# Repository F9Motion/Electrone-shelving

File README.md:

# RGB Lamp

A electronic shelving (1.8m) to put your other projects here. This is simple shelving called electronic because the shleving have a 8 RGB Lamps in top every shelf. You can just download materials and print/solder this :)

## Why I made this
I find shelving like this in marketplace but not electronic and take idea :D

## Features

- 7 modes: Aqua, White, Yellow, Red, Purple, Blue, Green, Lime, Indigo, Soft Peach
- Brightness from 10% to 100% in steps of 10%
- Settings (mode and brightness) are saved and restored after power loss
- Custom round PCB designed in KiCad
- USB-C powered

## Pictures

### Full 3D model

### PCB

## How it works
It works (RGB Lamps) with batery and firmware. Without firmware this shelving transforms to defoult shelving. Prease use with firmware!

## Controls

| Action                          | Result                          |
|---------------------------------|---------------------------------|
| Button 1: hold for 2 seconds    | Turn the lamp on / off (fade)   |
| Button 1: short press           | Next mode                       |
| Button 1: double press          | Brightness +10%                 |
| Button 2: short press           | Previous mode                   |
| Button 2: quick repeated press  | Brightness −10%                 |

## How to assemble
1. Print the PCB from JLPPCB's website or app
2. Print all .step files
3. Upload firmware to PCB
4. Collect all components(Take a look at the screenshots if you're having trouble)
5. Place it on your room and continue doing your other projects.

## Role of hack club
All this project will be sponsered by Hack club forge. A lot of thanks for you. You helped me do my dreams in real life. Hack club is working since 2015 so A new era of engineers is approaching. 

## How to flash

1. Install [Thonny](https://thonny.org/).
2. Flash MicroPython to the ESP32 (Thonny: *Tools → Options → Interpreter → Install or update MicroPython*).
3. Open `firmware/firmware.py` in Thonny.
4. Save it to the board as `main.py` (*File → Save as → MicroPython device*).
5. Restart the board. The OLED shows a loading bar and the lamp is ready.

## Bill of Materials (BOM)
|Name                                |Cost   |Link                                                                                                                                                           |
|------------------------------------|-------|---------------------------------------------------------------------------------------------------------------------------------------------------------------|
|ESP32 C3                            |$1.8   |https://aliexpress.ru/item/1005007676793679.html?shpMethod=AE_CN_SUPER_ECONOMY_G&sku_id=12000041769821205&spm=a2g2w.productlist.search_results.4.677f53633EnYjH|
|Diodes 1n4148                       |$0.7   |https://aliexpress.ru/item/1005007807649334.html?shpMethod=AE_CN_SUPER_ECONOMY_G&sku_id=12000042270438468&spm=a2g2w.productlist.search_results.2.1b7fad9fg6OJxq|
|RGB diodes                          |$18.54 |https://aliexpress.ru/item/1005002055349908.html?shpMethod=AE_CN_SUPER_ECONOMY_G&sku_id=12000034806960298&spm=a2g2w.productlist.search_results.2.7ffc338eJBxLZL|
|OLED display                        |$1.35  |https://aliexpress.ru/item/1005004572487969.html?shpMethod=AE_CN_SUPER_ECONOMY_G&sku_id=12000029674573173&spm=a2g2w.productlist.search_results.0.52ee537fxKO4CA|
|Buttons                             |$1.1   |https://aliexpress.ru/item/1005008653041072.html?shpMethod=CAINIAO_STANDARD&sku_id=12000046105949461&spm=a2g2w.productlist.search_results.17.67561fadfEL0GK    |
|Buzzer                              |$1.36  |https://aliexpress.ru/item/1005006000025929.html?shpMethod=AE_CN_SUPER_ECONOMY_G&sku_id=12000059707835705&spm=a2g2w.productlist.search_results.3.17d02d3defQwav|
|Socket                              |$2.08  |https://aliexpress.ru/item/1005009725016771.html?spm=a2g2w.cart.cart_split.15.6b284aa6VQwMUn&sku_id=12000049959236831                                          |
|Felament price for all of step files|       |                                                                                                                                                               |
|All step files                      |$489.45|                                                                                                                                                               |
| Print PCB | $11 |

## Credits
- CAD: Blender, PCB: KiCad
- Everything else (design, PCB, firmware): Rasul

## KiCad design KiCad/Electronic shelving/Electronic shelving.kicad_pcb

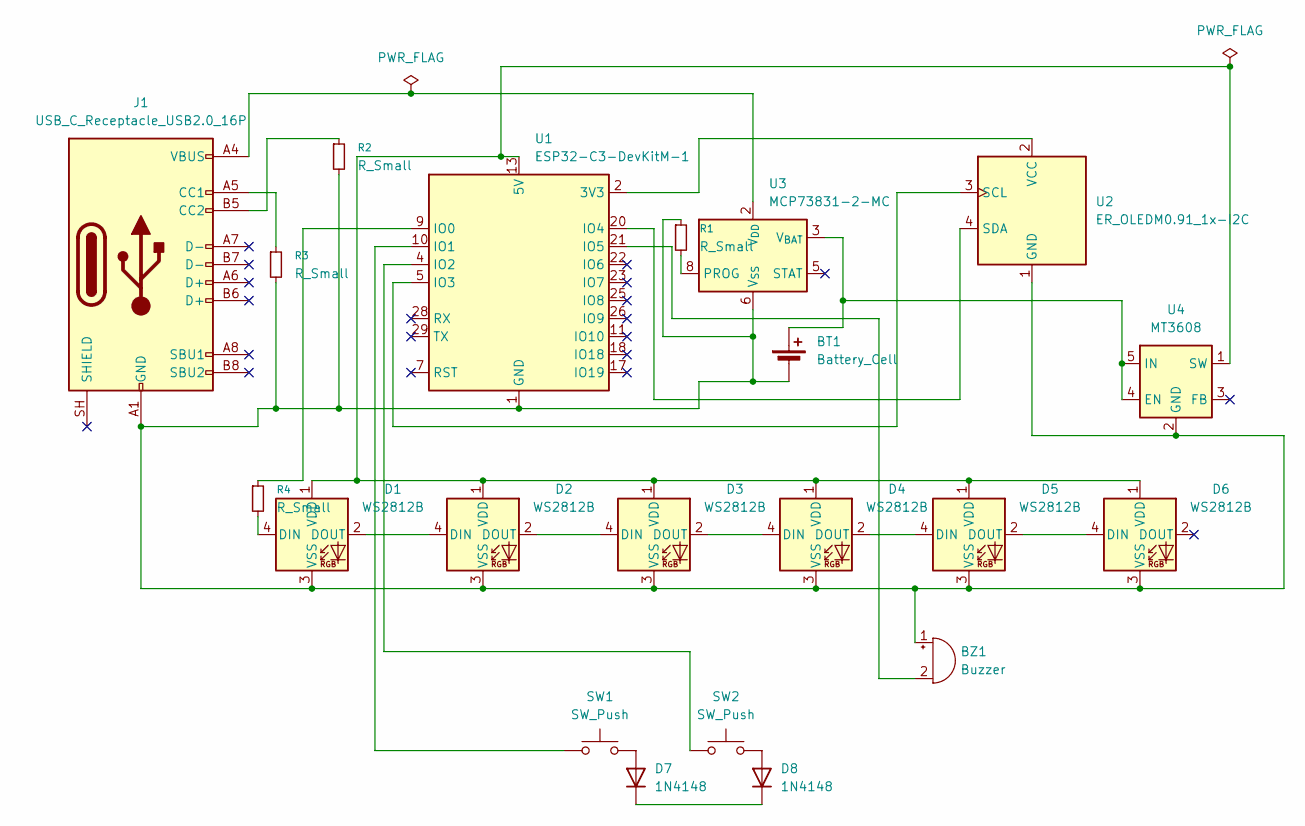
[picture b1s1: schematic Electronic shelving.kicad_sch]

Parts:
BT1: Battery_Cell; JST_PH_B2B-PH-K_1x02_P2.00mm_Vertical
BZ1: Buzzer; Buzzer_12x9.5RM7.6
D1, D2, D3, D4, D5, D6: WS2812B; LED_WS2812B_PLCC4_5.0x5.0mm_P3.2mm
D7, D8: 1N4148; LED_WS2812B_PLCC4_5.0x5.0mm_P3.2mm
J1: USB_C_Receptacle_USB2.0_16P; USB_C_Receptacle_Amphenol_124019772112A
R1, R2, R3, R4: R_Small; R_0805_2012Metric
SW1, SW2: SW_Push; SW_SPST_PTS645Sx43SMTR92
U1: ESP32-C3-DevKitM-1
U2: ER_OLEDM0.91_1x-I2C
U3: MCP73831-2-MC; DFN-8-1EP_3x2mm_P0.5mm_EP1.7x1.4mm
U4: MT3608; SOT-23-6

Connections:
unnamed: BT1.1 (+), U3.3 (V_{BAT}), U3.4 (V_{BAT}), U4.4 (EN), U4.5 (IN)
unnamed: BT1.2 (-), BZ1.1 (+), D1.3 (VSS), D2.3 (VSS), D3.3 (VSS), D4.3 (VSS), D5.3 (VSS), D6.3 (VSS), J1.A1 (GND), J1.A12 (GND), J1.B1 (GND), J1.B12 (GND), R1.1, R2.2, R3.2, U1.1 (GND), U1.6 (GND), U1.8 (GND), U1.12 (GND), U1.15 (GND), U1.16 (GND), U1.19 (GND), U1.24 (GND), U1.27 (GND), U1.30 (GND), U2.1 (GND), U3.6 (V_{SS}), U4.2 (GND)
unnamed: BZ1.2 (-), U1.21 (IO5)
unnamed: D1.4 (DIN), R4.2
unnamed: D1.2 (DOUT), D2.4 (DIN)
unnamed: D1.1 (VDD), D2.1 (VDD), D3.1 (VDD), D4.1 (VDD), D5.1 (VDD), D6.1 (VDD), U1.13 (5V), U1.14 (5V), U4.1 (SW)
unnamed: D2.2 (DOUT), D3.4 (DIN)
unnamed: D3.2 (DOUT), D4.4 (DIN)
unnamed: D4.2 (DOUT), D5.4 (DIN)
unnamed: D5.2 (DOUT), D6.4 (DIN)
unnamed: D7.2 (A), SW1.2
unnamed: D7.1 (K), D8.1 (K)
unnamed: D8.2 (A), SW2.2
unnamed: J1.A5 (CC1), R3.1
unnamed: J1.B5 (CC2), R2.1
unnamed: J1.A4 (VBUS), J1.A9 (VBUS), J1.B4 (VBUS), J1.B9 (VBUS), U3.1 (V_{DD}), U3.2 (V_{DD})
unnamed: R4.1, U1.9 (IO0)
unnamed: SW1.1, U1.10 (IO1)
unnamed: SW2.1, U1.4 (IO2)
unnamed: U1.5 (IO3), U2.3 (SCL)
unnamed: U1.20 (IO4), U2.4 (SDA)
unnamed: U1.2 (3V3), U1.3 (3V3), U2.2 (VCC)
unnamed: R1.2, U3.8 (PROG)

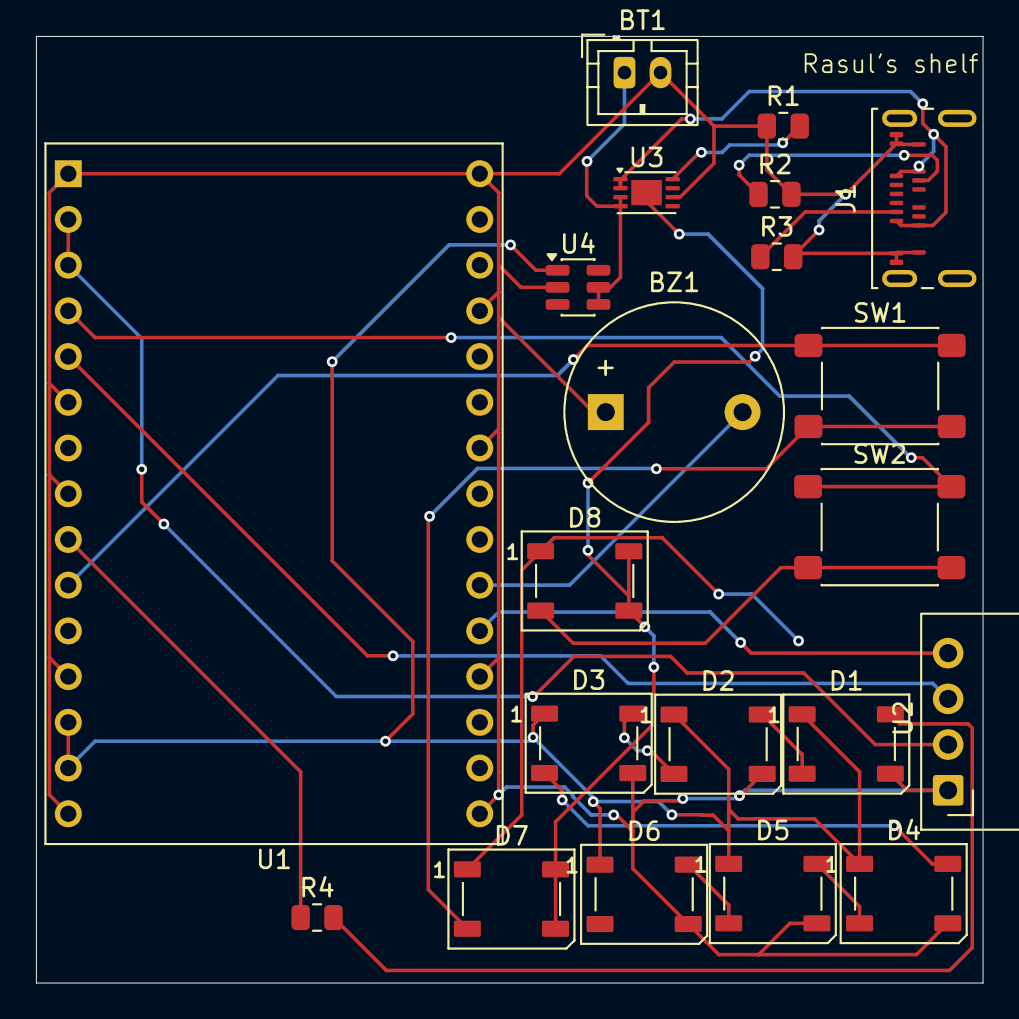
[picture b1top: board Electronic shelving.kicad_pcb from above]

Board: 2 copper layers, 52.6 x 52.6 mm, 21 parts (0 on the bottom side), 23 nets.
